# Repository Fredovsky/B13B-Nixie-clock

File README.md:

# B13B-Nixie-clock
Nixie clock made from F9057 Nixie tubes (B13B sockets).

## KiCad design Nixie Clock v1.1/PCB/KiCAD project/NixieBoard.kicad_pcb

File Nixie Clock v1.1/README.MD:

# Nixie Tube Desk Clock

A beautiful 4-digit nixie tube clock powered by an ATmega328P microcontroller, featuring automatic brightness adjustment and anti-cathode poisoning routines.

## Features

- **4-Digit Time Display**: Shows hours and minutes in HH:MM format
- **Automatic Brightness Control**: Gradually adjusts brightness throughout the day based on time (no light sensor required)
- **Cathode Poisoning Prevention**: Automatic cleaning cycles to maintain nixie tube health
  - Short cycle every hour (15 seconds)
  - Long cycle daily at 3:00 AM (30 minutes)
- **Simple Time Setting**: Two-button interface (Hour/Minute) with auto-repeat on long press
- **RTC Backup**: DS3231 real-time clock with battery backup maintains accurate time
- **Visual Error Indicators**: Blinking display indicates RTC issues or power loss

## Version 1.1 Changes

This version (v1.1) includes several improvements over v1.0:

### Hardware Changes
- **Simplified button interface**: 2 buttons (Hour/Minute) instead of 3 (Mode/+/-)
- **Removed brightness sensor**: Automatic brightness adjustment is now time-based via software
- **Display mode**: Time only (no date/year display modes)
- **PCB redesign**: Now in KiCad format (previously Eagle)

### Software Improvements
- Restored and improved blinking functionality for error indication
- Removed blocking delays from button handling for better responsiveness
- Implemented proper auto-repeat for time adjustment buttons
- Added RTC communication error detection
- Cleaned up code structure with named constants
- Optimized SPI communication
- Fixed potential brightness range bugs

*Code cleaned and improved with assistance from Claude AI*

## Hardware Components

### Main Festures
- **Microcontroller**: ATmega328P
- **RTC Module**: DS3231 with CR2032 battery backup
- **Nixie Tubes**: 4× B31B socket tubes (10-digit tubes)
- **High Voltage Drivers**: 2× HV5530 (32-bit shift registers)

### Pin Assignments
```
Pin 6:  Hour button input
Pin 7:  Minute button input
Pin 9:  PWM output for brightness control
Pin 10: SPI latch pin for HV5530
Pin 11: SPI MOSI (to HV5530)
Pin 13: SPI SCK (to HV5530)
```

## Project Files

### PCB Design
The `PCB/` folder contains:
- KiCad project files (.kicad_pro, .kicad_sch, .kicad_pcb)
- Gerber files for PCB manufacturing
- Bill of Materials (BOM)

### 3D Printed Case
The `3D Files/` folder contains:
- STL files for case components
- CAD source files

### Firmware
- `main.cpp`: Arduino-compatible C++ code for ATmega328P
- Uses Arduino framework with RTClib library (v1.12.4)

## Software Configuration

### Brightness Settings
Automatic brightness adjustment can be customized:

```cpp
uint8_t minBrightness = 15;        // Minimum PWM (0-255)
uint8_t maxBrightness = 240;       // Maximum PWM (0-255)
uint8_t timeStartDecrease = 19;    // Hour to start dimming (24h format)
uint8_t timeStartIncrease = 6;     // Hour to start brightening (24h format)
```

**How it works:**
- Brightness gradually decreases from 7 PM (19:00) to 6 AM
- Brightness gradually increases from 6 AM to 7 PM
- Changes by 1 PWM unit per minute (~3.75 hours for full transition)

### Cathode Poisoning Prevention
```cpp
constexpr uint8_t CLEANING_HOUR = 3;  // Hour for long cleaning cycle (3 AM)
```

The clock automatically cycles through all digits to prevent cathode poisoning:
- **Short cycle**: Every hour on the hour (except at cleaning hour) - 15 seconds
- **Long cycle**: Daily at 3:00 AM - 30 minutes

## Building and Uploading

### Requirements
- PlatformIO
- USBasp, Arduino as ISP, or similar programmer for ATmega328P

### Setting Initial Time
If the RTC has lost power (battery dead or first-time setup):
1. The display will show `00:00` blinking
2. Use Hour and Minute buttons to set the correct time
3. Blinking stops once you press a button (confirms time set)

## Usage

### Normal Operation
- Display shows current time in HH:MM format
- Brightness adjusts automatically throughout the day
- Cathode cleaning cycles run automatically

### Setting Time
- **Short press Hour button**: Increment hour by 1
- **Long press Hour button**: Auto-repeat (fast increment)
- **Short press Minute button**: Increment minute by 1
- **Long press Minute button**: Auto-repeat (fast increment)

### Error Indicators
- **Blinking 88:88**: RTC communication error
- **Blinking 00:00**: RTC lost power (battery dead or removed - set time)

## Troubleshooting

### Display shows 00:00 blinking
- Replace CR2032 battery in DS3231 module
- Set time using Hour/Minute buttons

### Tubes don't light up
- Check high voltage power supply (~170V)
- Verify HV5530 connections and power
- Test SPI communication (MOSI, SCK, Latch)

### Time drifts
- DS3231 is very accurate (±2ppm)
- Check RTC battery voltage
- Ensure crystal is functioning

## License

MIT License

Copyright (c) 2025 Frederic Lidove

Permission is hereby granted, free of charge, to any person obtaining a copy
of this software and associated documentation files (the "Software"), to deal
in the Software without restriction, including without limitation the rights
to use, copy, modify, merge, publish, distribute, sublicense, and/or sell
copies of the Software, and to permit persons to whom the Software is
furnished to do so, subject to the following conditions:

The above copyright notice and this permission notice shall be included in all
copies or substantial portions of the Software.

THE SOFTWARE IS PROVIDED "AS IS", WITHOUT WARRANTY OF ANY KIND, EXPRESS OR
IMPLIED, INCLUDING BUT NOT LIMITED TO THE WARRANTIES OF MERCHANTABILITY,
FITNESS FOR A PARTICULAR PURPOSE AND NONINFRINGEMENT.

## Credits

- Hardware design: Frederic Lidove
- Firmware v1.1: Code improvements by Claude AI (Anthropic)

## Changelog

### v1.1 (Current)
- Simplified to 2-button interface (H/M only)
- Removed hardware brightness sensor
- Implemented software-based automatic brightness adjustment
- Removed date/year display modes (time only)
- PCB redesigned in KiCad
- Code cleanup and optimization
- Improved error handling and blinking indicators

### v1.0
- Initial release
- 3-button interface (Mode/+/-)
- Hardware brightness sensor
- Date and year display modes
- Eagle PCB design

## Contributing

Contributions are welcome! Please feel free to submit pull requests or open issues for bugs and feature requests.

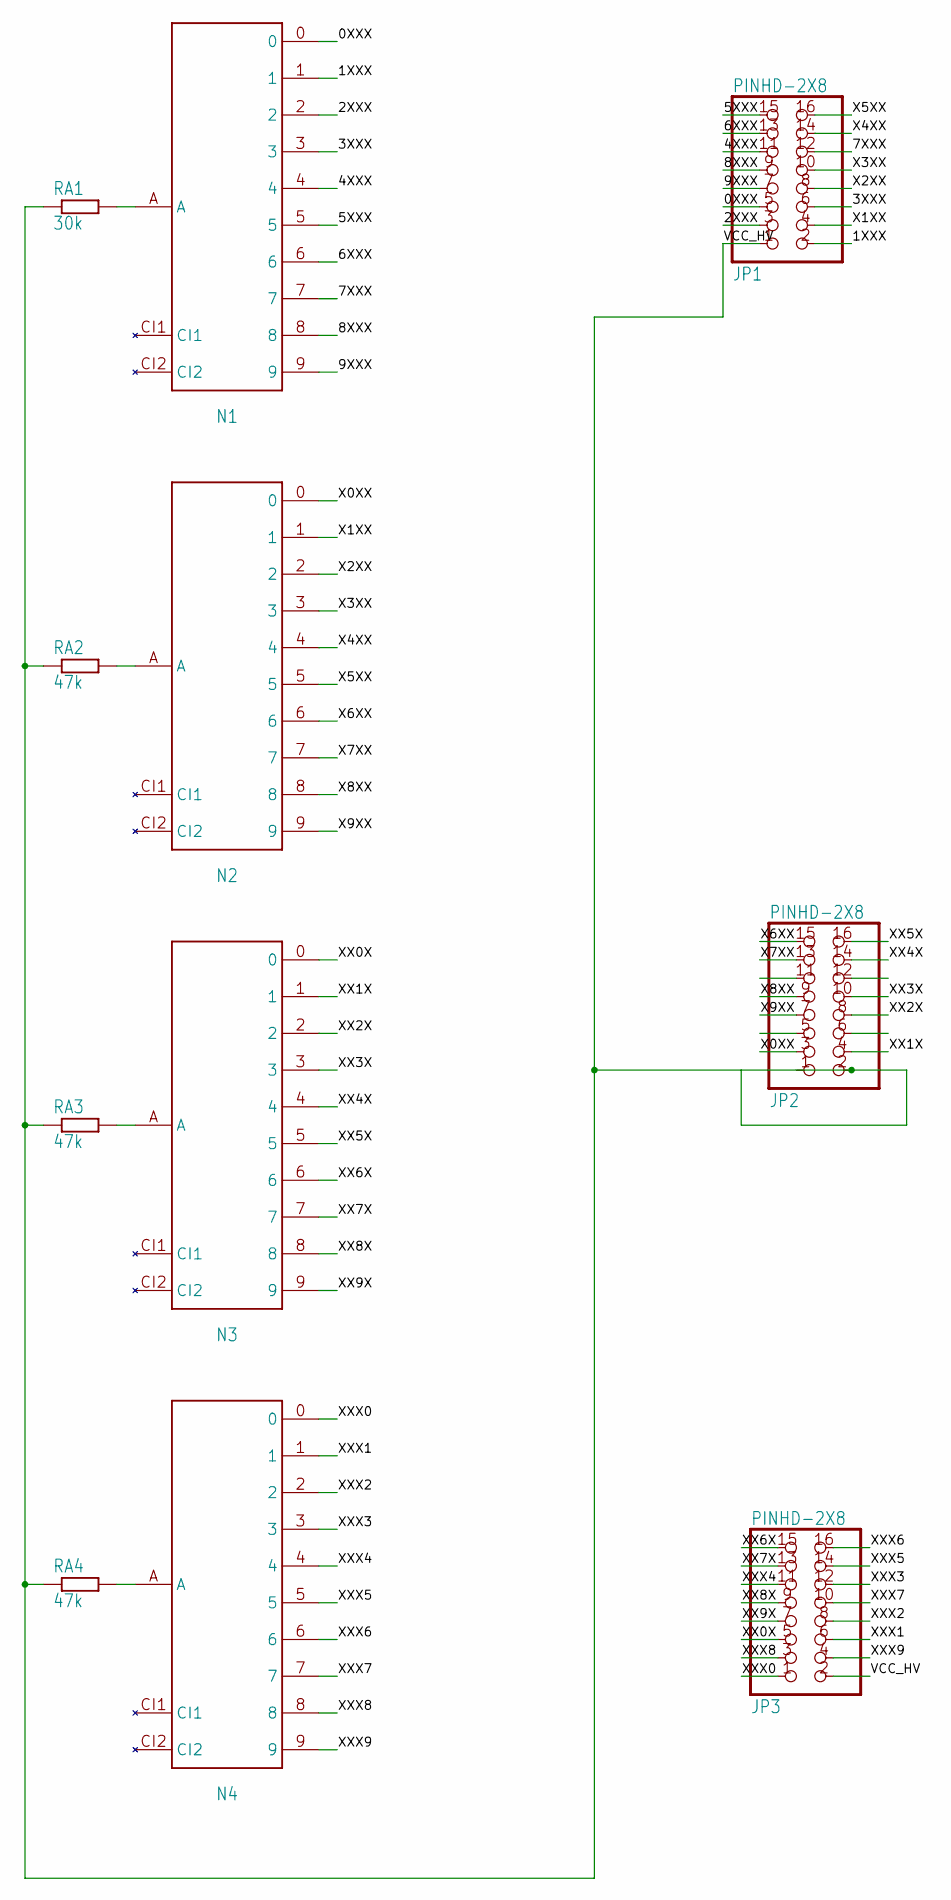
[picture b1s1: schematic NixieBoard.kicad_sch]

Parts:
JP1, JP2, JP3: PINHD-2X8; 2X08
N1, N2, N3, N4: F9057TUBE; F9057PIN
RA1: 30k; R2010
RA2, RA3, RA4: 47k; R2010

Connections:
0XXX: JP1.5, N1.0
1XXX: JP1.2, N1.1
2XXX: JP1.3, N1.2
3XXX: JP1.6, N1.3
4XXX: JP1.11, N1.4
5XXX: JP1.15, N1.5
6XXX: JP1.13, N1.6
7XXX: JP1.12, N1.7
8XXX: JP1.9, N1.8
9XXX: JP1.7, N1.9
unnamed: N4.A, RA4.2
unnamed: N3.A, RA3.2
unnamed: N2.A, RA2.2
unnamed: N1.A, RA1.2
VCC_HV: JP1.1, JP2.1, JP2.2, JP3.2, RA1.1, RA2.1, RA3.1, RA4.1
X0XX: JP2.3, N2.0
X1XX: JP1.4, N2.1
X2XX: JP1.8, N2.2
X3XX: JP1.10, N2.3
X4XX: JP1.14, N2.4
X5XX: JP1.16, N2.5
X6XX: JP2.15, N2.6
X7XX: JP2.13, N2.7
X8XX: JP2.9, N2.8
X9XX: JP2.7, N2.9
XX0X: JP3.5, N3.0
XX1X: JP2.4, N3.1
XX2X: JP2.8, N3.2
XX3X: JP2.10, N3.3
XX4X: JP2.14, N3.4
XX5X: JP2.16, N3.5
XX6X: JP3.15, N3.6
XX7X: JP3.13, N3.7
XX8X: JP3.9, N3.8
XX9X: JP3.7, N3.9
XXX0: JP3.1, N4.0
XXX1: JP3.6, N4.1
XXX2: JP3.8, N4.2
XXX3: JP3.12, N4.3
XXX4: JP3.11, N4.4
XXX5: JP3.14, N4.5
XXX6: JP3.16, N4.6
XXX7: JP3.10, N4.7
XXX8: JP3.3, N4.8
XXX9: JP3.4, N4.9

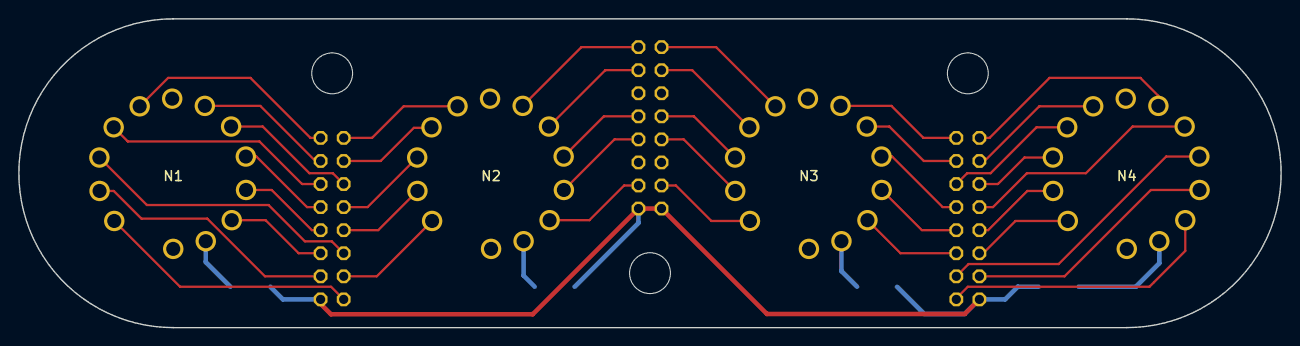
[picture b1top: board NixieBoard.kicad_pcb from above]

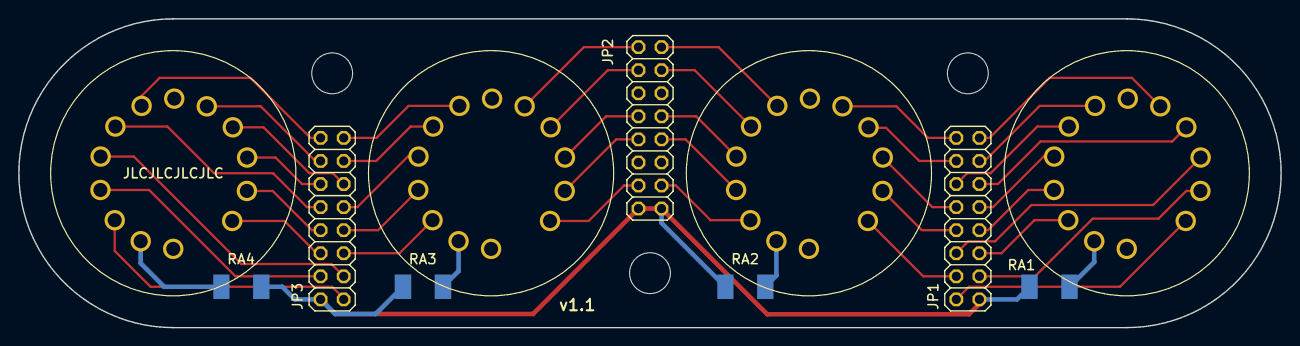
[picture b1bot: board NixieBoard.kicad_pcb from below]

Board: 2 copper layers, 139.0 x 34.0 mm, 14 parts (7 on the bottom side), 45 nets.

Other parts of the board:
UNK_HOLE_0: dummyfp0
UNK_HOLE_1: dummyfp1
UNK_HOLE_2: dummyfp2

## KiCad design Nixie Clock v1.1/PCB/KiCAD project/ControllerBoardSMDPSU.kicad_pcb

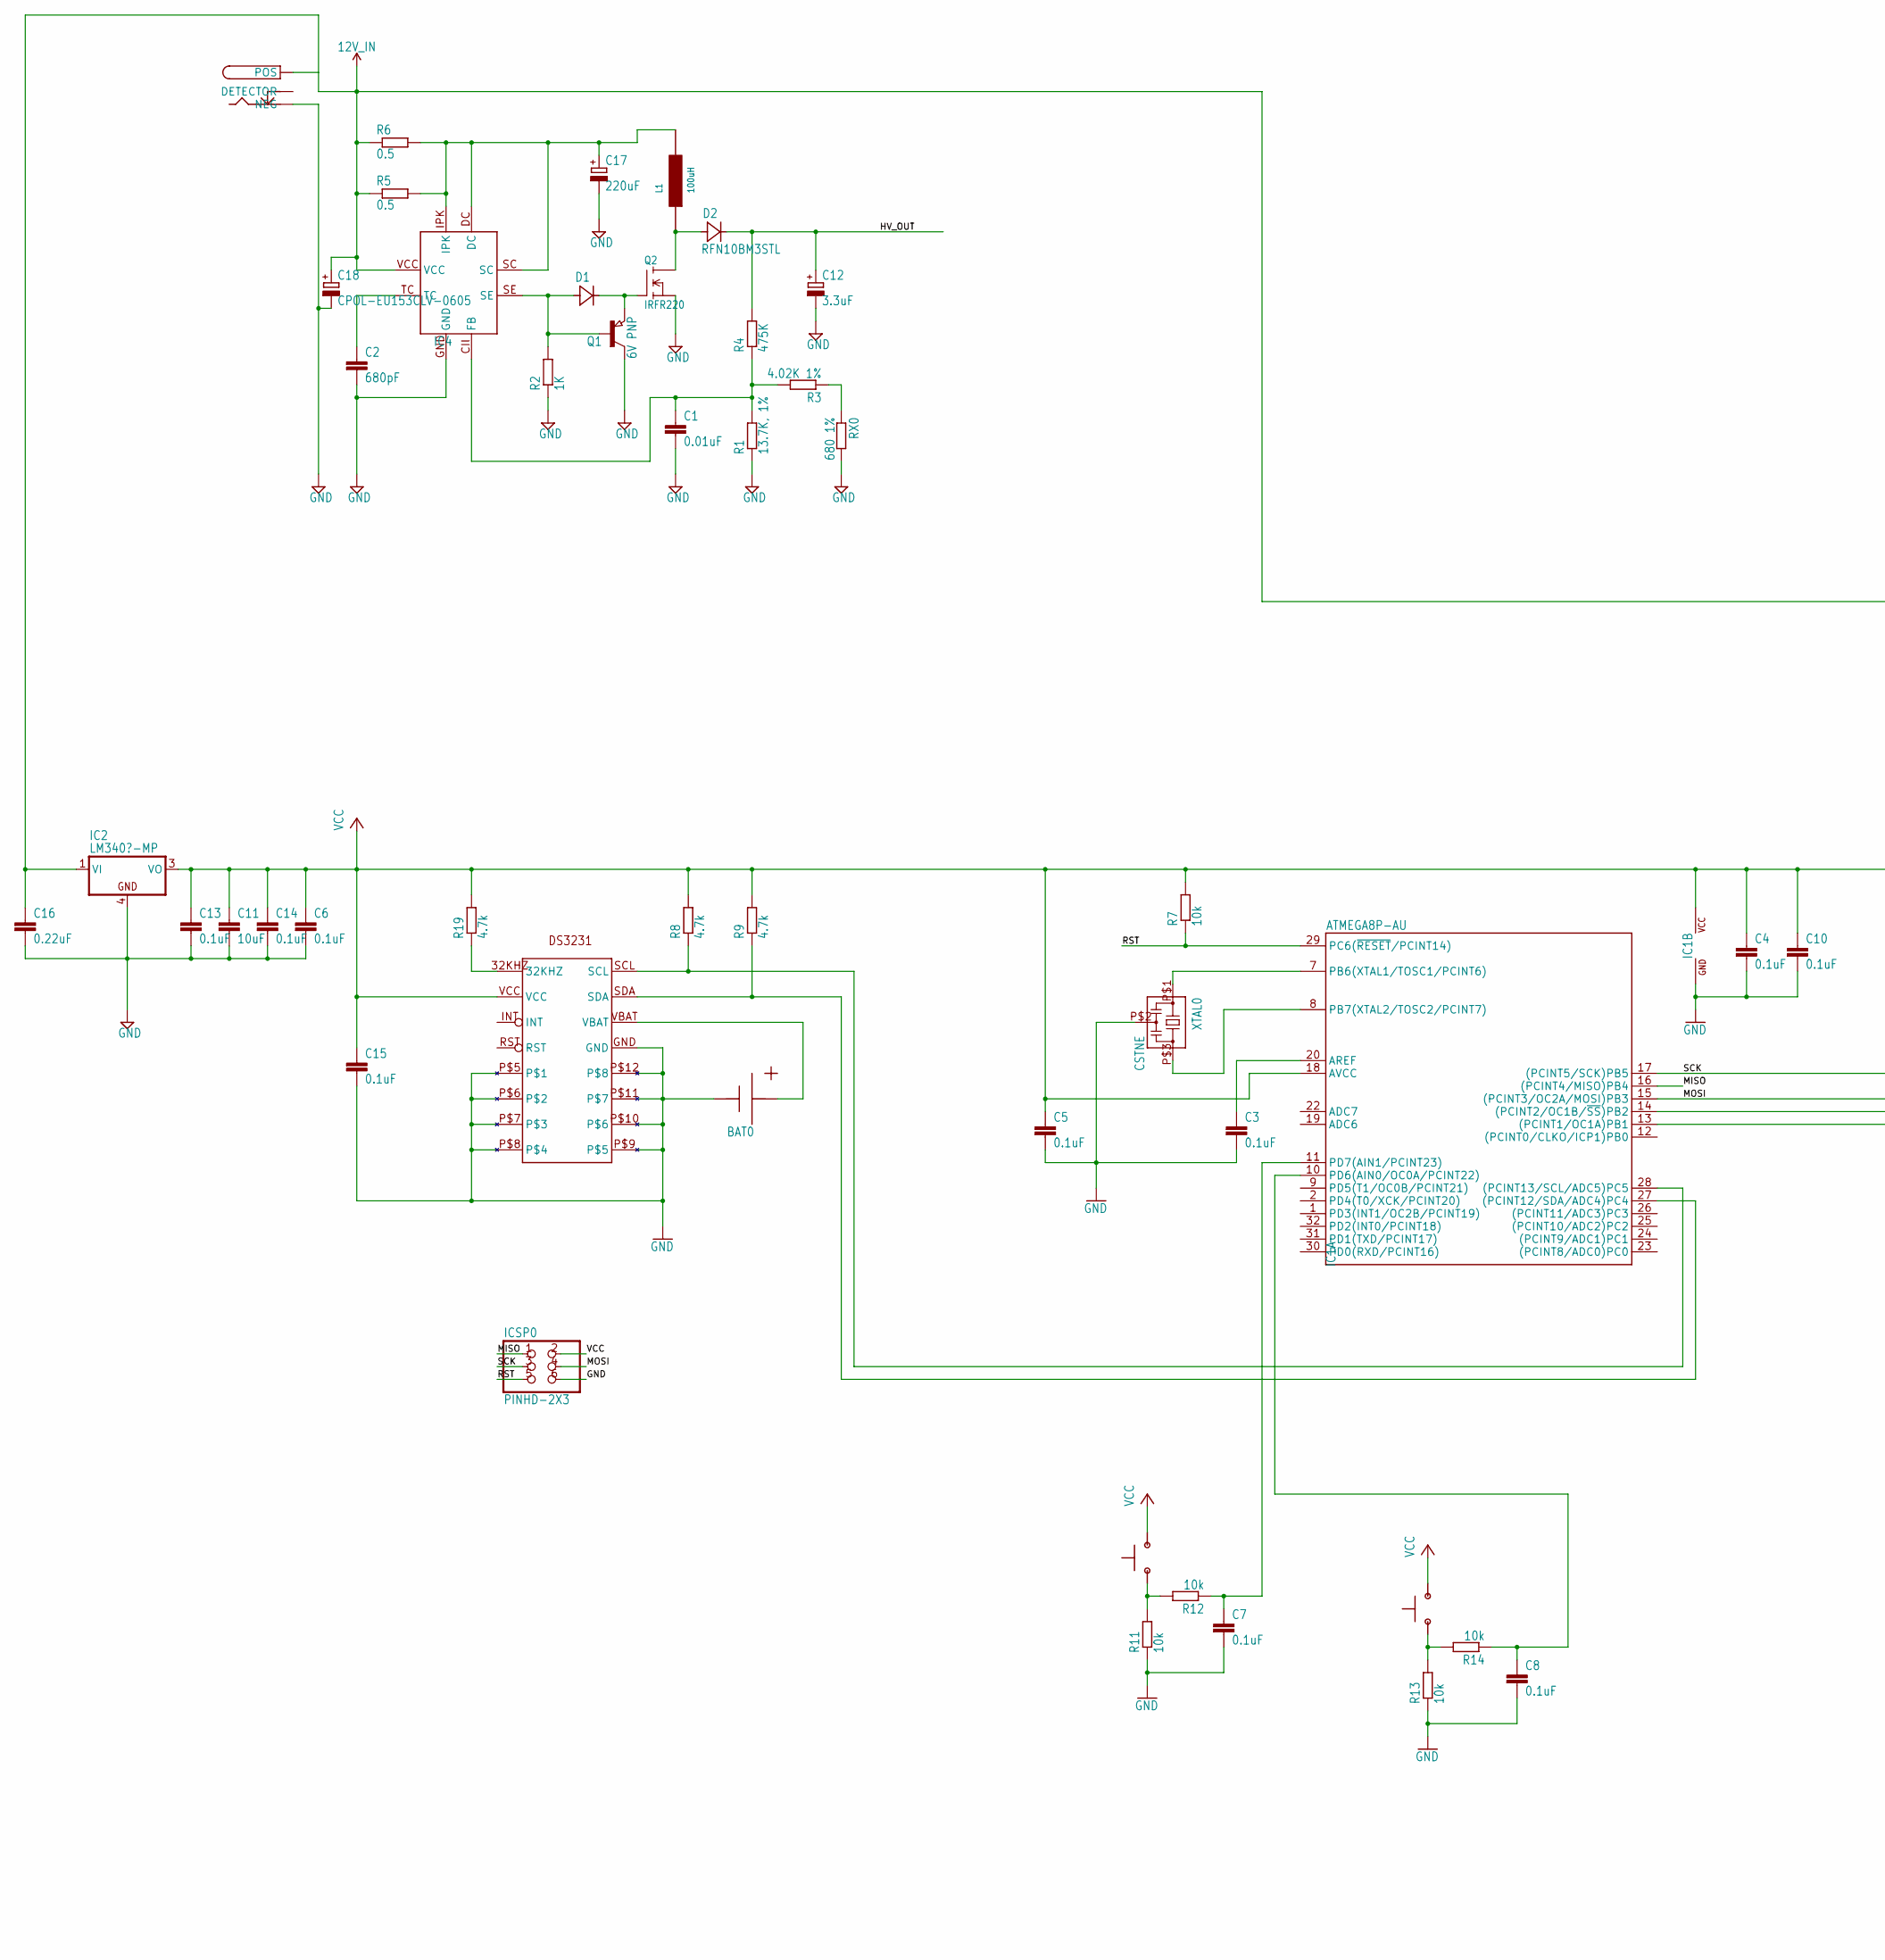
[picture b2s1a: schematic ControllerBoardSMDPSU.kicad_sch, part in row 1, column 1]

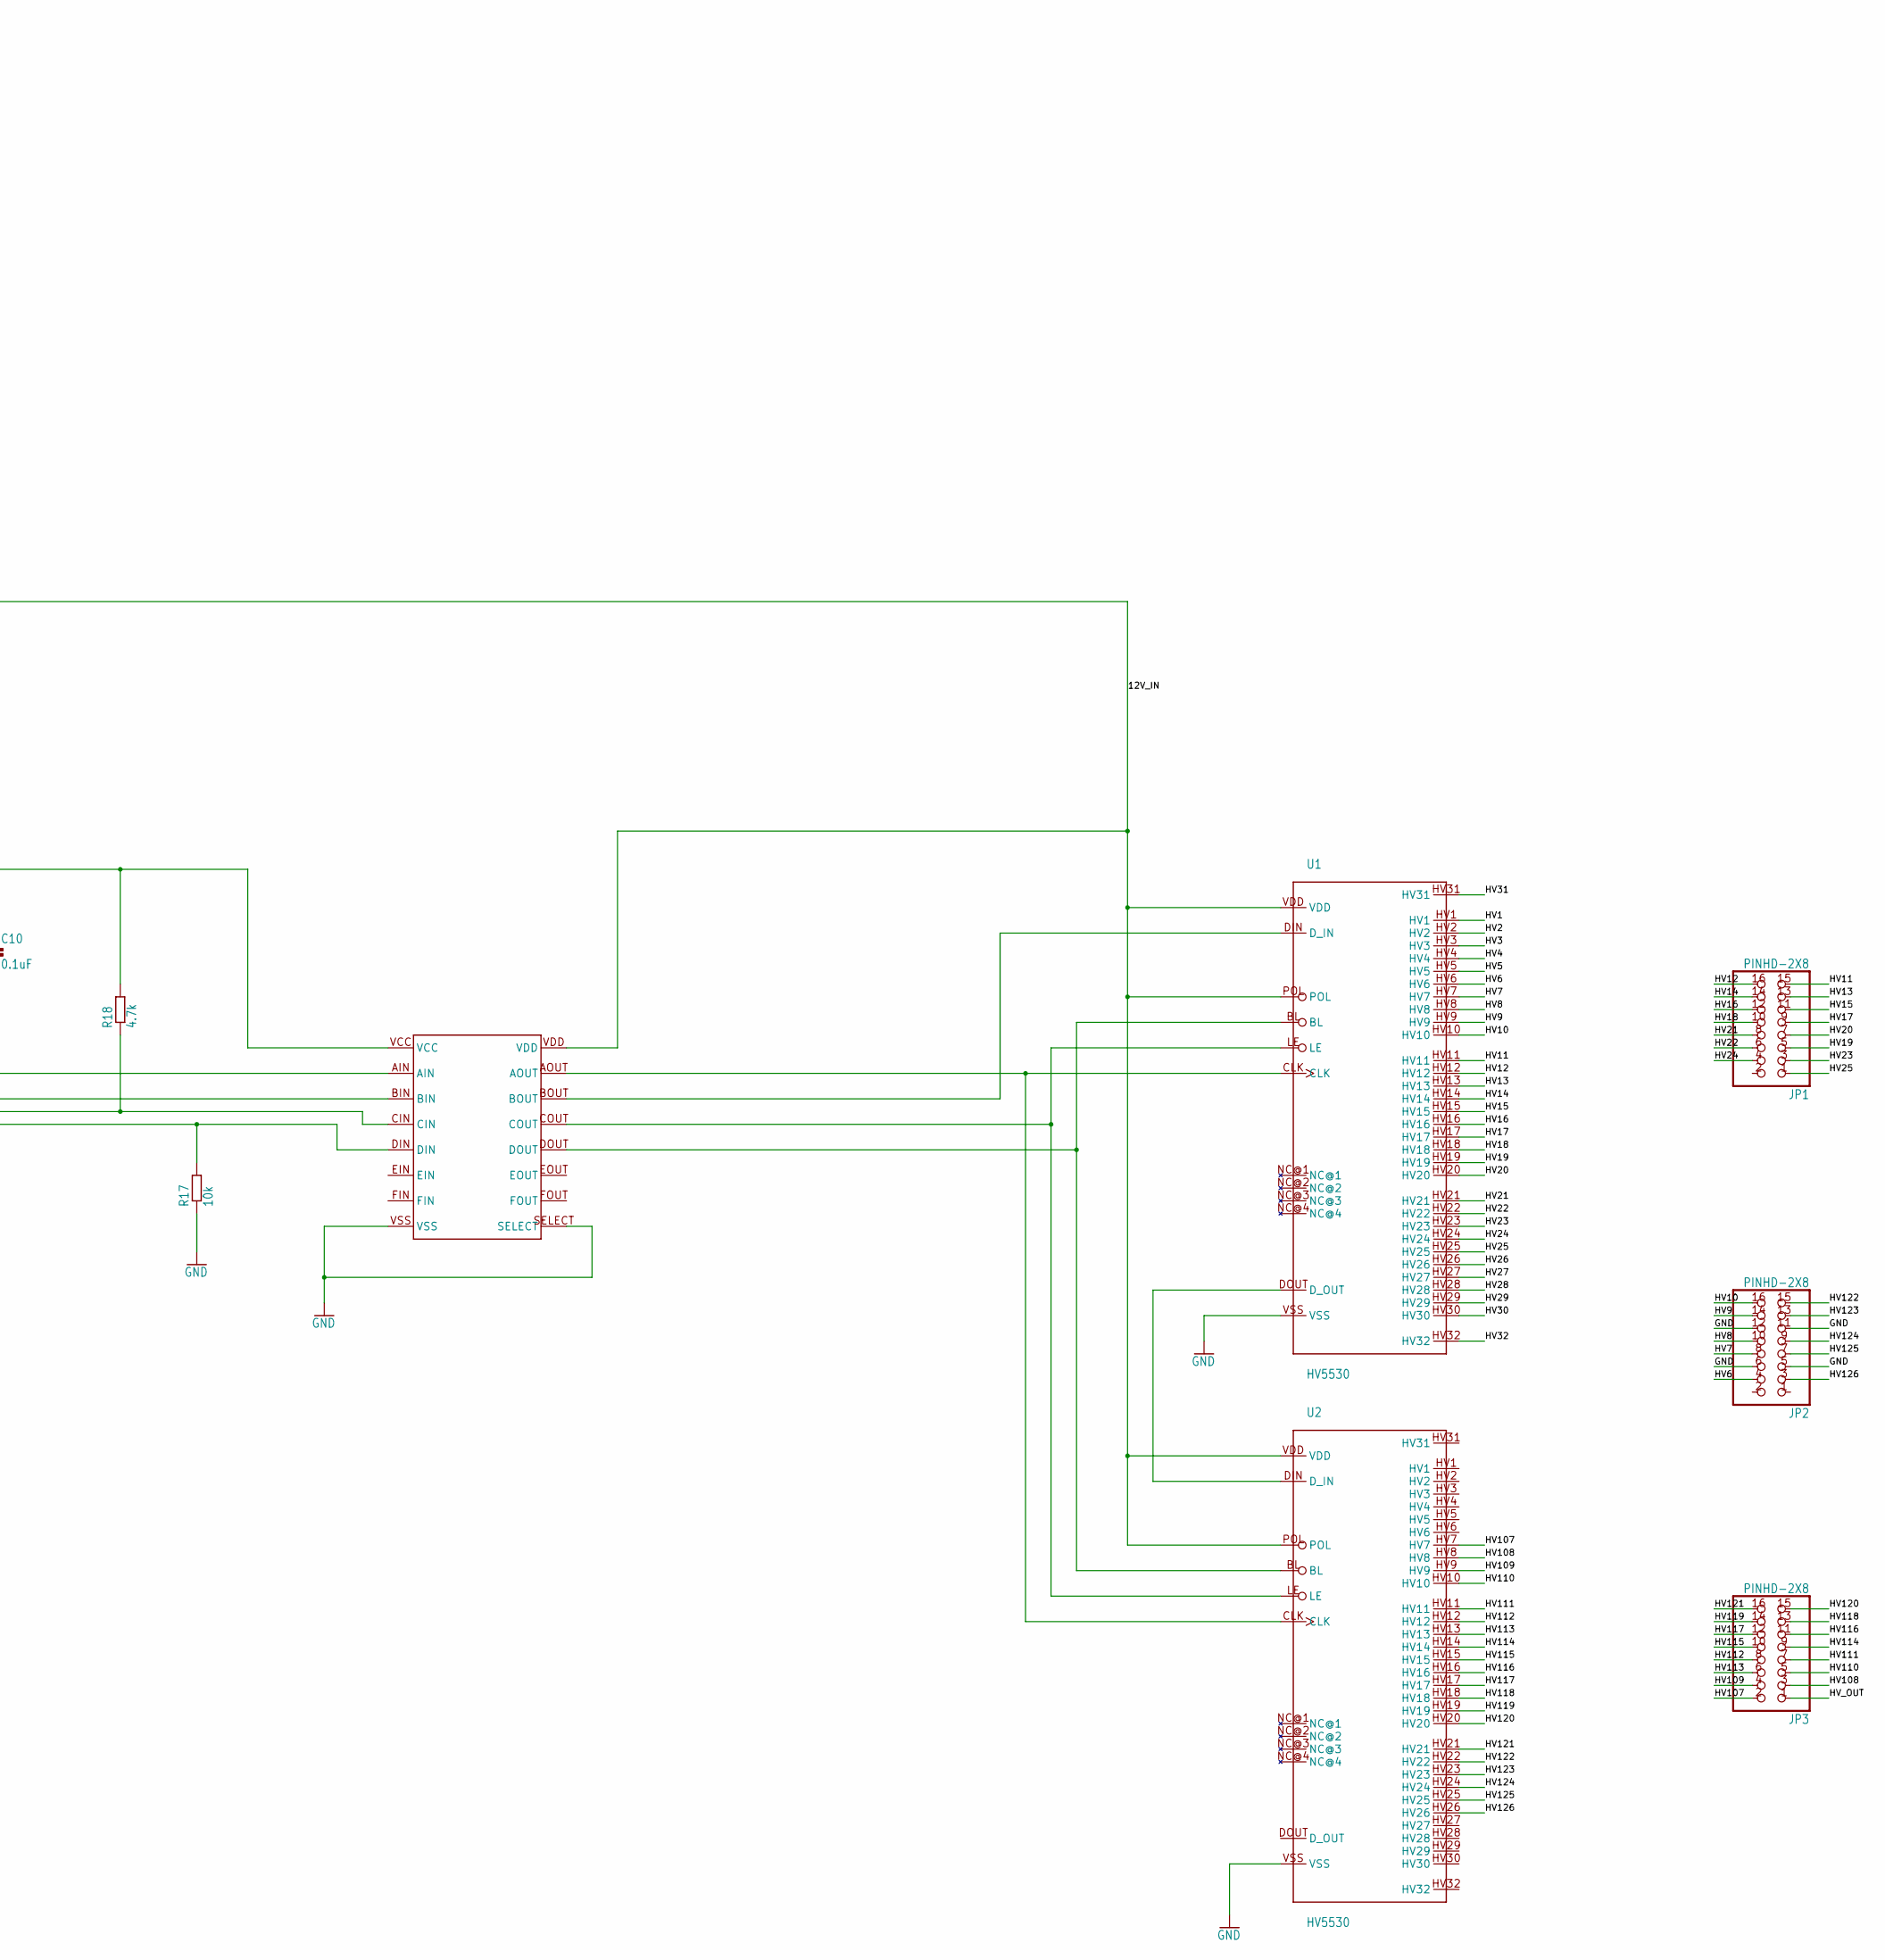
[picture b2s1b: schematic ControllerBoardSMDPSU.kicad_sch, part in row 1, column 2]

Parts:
BAT0: CR2032-SMD-HLDR; CR2032-SMD
C1: 0.01uF; C0603
C2: 680pF; C0603
C3, C4, C5, C6, C7, C8, C10, C13, C14, C15: 0.1uF; C0603
C11: 10uF; C0603
C12: 3.3uF; 153CLV-0810
C16: 0.22uF; C0603
C17: 220uF; 153CLV-0605
C18: CPOL-EU153CLV-0605; 153CLV-0605
D1: SOT123DIODE; SOD123
D2: RFN10BM3STL; TO252
IC1: ATMEGA8P-AU; QFP32_7X7_0.80
IC2: LM340?-MP; SOT223
IC3: CD4504BTSSOP16; SOP65P640X120-16N
IC4: MC34063; SOIC127P600X175-8
ICSP0: PINHD-2X3; 2X03
JP1, JP2, JP3: PINHD-2X8; 2X08
L1: 100uH; SDR1105
Q1: 6V PNP; SOT23
Q2: IRFR220; DPAK
R1: 13.7K, 1%; R1206
R2: 1K; R1206
R3: 4.02K 1%; R1206
R4: 475K; R1206
R5, R6: 0.5; R1206
R7, R11, R12, R13, R14, R17: 10k; R0603
R8, R9, R18, R19: 4.7k; R0603
RTC0: DS3231-CORRECT; SOIC16-CORRECT
RX0: 680 1%; R1206
S1, S2: TL1105
U1, U2: HV5530; 44_PQFP_CORRECTED
UNK12V0: CUI_PWR_JACK
XTAL0: CSTNE

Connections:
12V_IN: C16.1, C18.+, IC2.1 (VI), IC3.VDD, IC4.VCC, R5.1, R6.1, U1.POL, U1.VDD, U2.POL, U2.VDD, UNK12V0.POS, UNK12V0.POS1 (POS); also elsewhere on the board
/HV1: U1.HV1
/HV2: U1.HV2
/HV3: U1.HV3
/HV4: U1.HV4
/HV5: U1.HV5
/HV6: JP2.4, U1.HV6
/HV7: JP2.8, U1.HV7
/HV8: JP2.10, U1.HV8
/HV9: JP2.14, U1.HV9
/HV10: JP2.16, U1.HV10
/HV11: JP1.15, U1.HV11
/HV12: JP1.16, U1.HV12
/HV13: JP1.13, U1.HV13
/HV14: JP1.14, U1.HV14
/HV15: JP1.11, U1.HV15
/HV16: JP1.12, U1.HV16
/HV17: JP1.9, U1.HV17
/HV18: JP1.10, U1.HV18
/HV19: JP1.5, U1.HV19
/HV20: JP1.7, U1.HV20
/HV21: JP1.8, U1.HV21
/HV22: JP1.6, U1.HV22
/HV23: JP1.3, U1.HV23
/HV24: JP1.4, U1.HV24
/HV25: JP1.1, U1.HV25
/HV26: U1.HV26
/HV27: U1.HV27
/HV28: U1.HV28
/HV29: U1.HV29
/HV30: U1.HV30
/HV31: U1.HV31
/HV32: U1.HV32
/HV107: JP3.2, U2.HV7
/HV108: JP3.3, U2.HV8
/HV109: JP3.4, U2.HV9
/HV110: JP3.5, U2.HV10
/HV111: JP3.7, U2.HV11
/HV112: JP3.8, U2.HV12
/HV113: JP3.6, U2.HV13
/HV114: JP3.9, U2.HV14
/HV115: JP3.10, U2.HV15
/HV116: JP3.11, U2.HV16
/HV117: JP3.12, U2.HV17
/HV118: JP3.13, U2.HV18
/HV119: JP3.14, U2.HV19
/HV120: JP3.15, U2.HV20
/HV121: JP3.16, U2.HV21
/HV122: JP2.15, U2.HV22
/HV123: JP2.13, U2.HV23
/HV124: JP2.9, U2.HV24
/HV125: JP2.7, U2.HV25
/HV126: JP2.3, U2.HV26
/HV_OUT: C12.+, D2.3 (C), JP3.1, R4.2
/MISO: IC1.16 ((PCINT4/MISO)PB4), ICSP0.1; also elsewhere on the board
/MOSI: IC1.15 ((PCINT3/OC2A/MOSI)PB3), IC3.BIN, ICSP0.4; also elsewhere on the board
/RST: IC1.29 (PC6(~RESET/PCINT14)), ICSP0.5, R7.1; also elsewhere on the board
/SCK: IC1.17 ((PCINT5/SCK)PB5), IC3.AIN, ICSP0.3; also elsewhere on the board
GND: BAT0.NEG, C1.2, C2.2, C3.2, C4.2, C5.2, C6.2, C7.2, C8.2, C10.2, C11.2, C12.-, C13.2, C14.2, C15.2, C16.2, C17.-, C18.-, IC1.3 (GND), IC1.5 (GND), IC1.21 (GND), IC2.4 (GND), IC3.SELECT, IC3.VSS, IC4.GND, ICSP0.6, JP2.5, JP2.6, JP2.11, JP2.12, Q1.3 (C), Q2.3 (S), R1.1, R2.1, R11.1, R13.1, R17.1, RTC0.GND, RTC0.P$5, RTC0.P$6, RTC0.P$7, RTC0.P$8, RTC0.P$9, RTC0.P$10, RTC0.P$11, RTC0.P$12, RX0.2, U1.VSS, U2.VSS, UNK12V0.NEG, UNK12V0.NEG1 (NEG), XTAL0.P$2 (2); also elsewhere on the board
unnamed 59: BAT0.POS@1 (POS), BAT0.POS@2 (POS), RTC0.VBAT; also elsewhere on the board
unnamed: C2.1, IC4.TC
unnamed: C17.+, IC4.DC, IC4.IPK, IC4.SC, L1.P$2, R5.2, R6.2
unnamed: D1.2 (A), IC4.SE, Q1.1 (B), R2.2
unnamed: D1.1 (C), Q1.2 (E), Q2.1 (G)
unnamed: IC1.13 ((PCINT1/OC1A)PB1), IC3.DIN, R17.2
unnamed: IC1.14 ((PCINT2/OC1B/~SS)PB2), IC3.CIN, R18.1
unnamed 66: IC1.27 ((PCINT12/SDA/ADC4)PC4), R9.1, RTC0.SDA; also elsewhere on the board
unnamed 67: IC1.28 ((PCINT13/SCL/ADC5)PC5), R8.1, RTC0.SCL; also elsewhere on the board
unnamed: C3.1, IC1.20 (AREF)
unnamed 69: IC1.7 (PB6(XTAL1/TOSC1/PCINT6)), XTAL0.P$1 (1); also elsewhere on the board
unnamed 70: IC1.8 (PB7(XTAL2/TOSC2/PCINT7)), XTAL0.P$3 (3); also elsewhere on the board
unnamed: C8.1, IC1.10 (PD6(AIN0/OC0A/PCINT22)), R14.1
unnamed: C7.1, IC1.11 (PD7(AIN1/PCINT23)), R12.1
unnamed: IC3.AOUT, U1.CLK, U2.CLK
unnamed: IC3.COUT, U1.LE, U2.LE
unnamed: IC3.DOUT, U1.BL, U2.BL
unnamed: C1.1, IC4.CII (FB), R1.2, R3.2, R4.1
unnamed: D2.1 (A), D2.2 (A), L1.P$1, Q2.2 (D)
unnamed 78: R3.1, RX0.1; also elsewhere on the board
unnamed: R11.2, R12.2, S1.1, S1.2
unnamed: R13.2, R14.2, S2.1, S2.2
unnamed 81: R19.1, RTC0.32KHZ; also elsewhere on the board
unnamed: IC3.BOUT, U1.DIN (D_IN)
unnamed: U1.DOUT (D_OUT), U2.DIN (D_IN)
unnamed: UNK12V0.DETECTOR, UNK12V0.DETECTOR1 (DETECTOR)
VCC: C4.1, C5.1, C6.1, C10.1, C11.1, C13.1, C14.1, C15.1, IC1.4 (VCC), IC1.6 (VCC), IC1.18 (AVCC), IC2.3 (VO), IC3.VCC, R7.2, R8.2, R9.2, R18.2, R19.2, RTC0.VCC, S1.3, S1.4, S2.3, S2.4; also elsewhere on the board

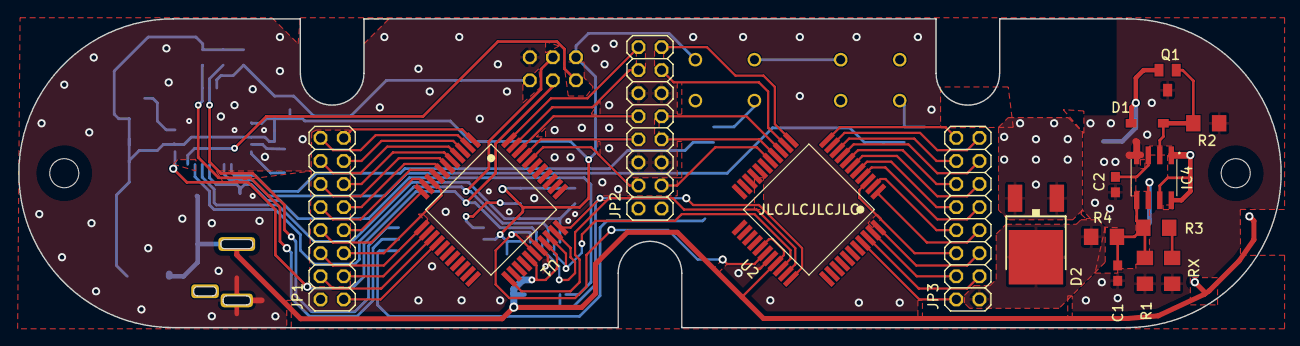
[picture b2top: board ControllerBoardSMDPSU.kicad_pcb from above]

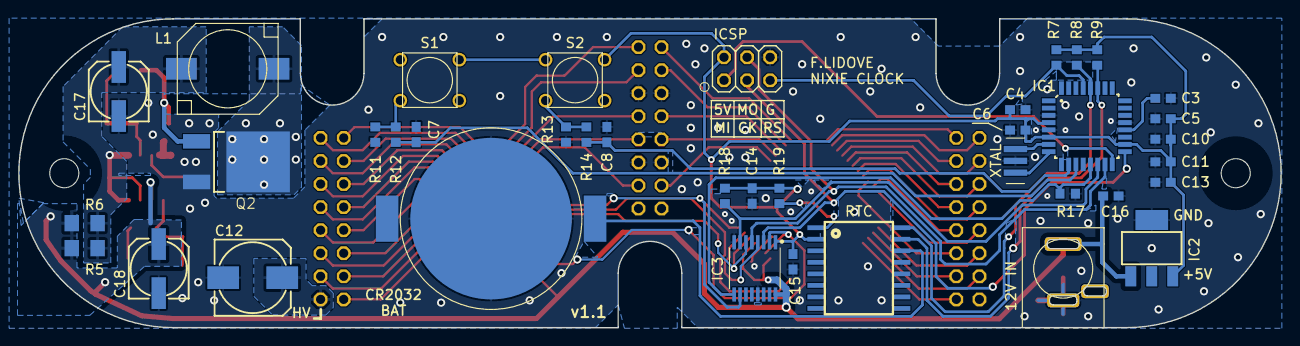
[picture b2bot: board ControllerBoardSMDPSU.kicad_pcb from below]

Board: 2 copper layers, 139.0 x 34.0 mm, 55 parts (39 on the bottom side), 74 nets.

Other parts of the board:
12V IN: CUI_PWR_JACK
ICSP: PINHD-2X3; 2X03_325
RTC: DS3231-CORRECT; SOIC16-CORRECT
RX: 680 1%; R1206_334
XTAL: CSTNE

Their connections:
12V_IN: 12V IN.POS, 12V IN.POS1 (POS); also elsewhere on the board
/MISO: ICSP.1; also elsewhere on the board
/MOSI: ICSP.4; also elsewhere on the board
/RST: ICSP.5; also elsewhere on the board
/SCK: ICSP.3; also elsewhere on the board
GND: 12V IN.NEG, 12V IN.NEG1 (NEG), ICSP.6, RTC.GND, RX.2, XTAL.P$2 (2); also elsewhere on the board
unnamed 59: RTC.VBAT; also elsewhere on the board
unnamed 66: RTC.SDA; also elsewhere on the board
unnamed 67: RTC.SCL; also elsewhere on the board
unnamed 69: XTAL.P$1 (1); also elsewhere on the board
unnamed 70: XTAL.P$3 (3); also elsewhere on the board
unnamed 78: RX.1; also elsewhere on the board
unnamed 81: RTC.32KHZ; also elsewhere on the board
unnamed: 12V IN.DETECTOR, 12V IN.DETECTOR1 (DETECTOR)
VCC: ICSP.2, RTC.VCC; also elsewhere on the board

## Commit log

2021-03-23 Project creation
    Added all project files.
2021-03-23 Reorganized files and added PCB BOM.
    Bill of materials added for V1 of the clock PCB using SMD for PSU.
2021-12-12 First flash CPU clock bug fix
    RTCLib version added and CPU clock speed protocol for first upload.
2021-12-23 Update main.cpp
    Long Cathode Poisoning Prevention Routine set for 30min at 3am, short routine every hour for 15 seconds.
2025-10-16 Added v1.1
    v1.1 = modified Control board and back board for simpler 2-buttons set up (no more date/year functionnality as it was useless).
    PCBs now all on KiCAD.
    Added an updated BOM and 3D Print files if unable to make wooden case.
2025-12-12 Set CPU frequency to 16MHz and configure fuses
    Updated CPU frequency to 16MHz and added fuse settings for external crystal.
2025-12-12 Add temporary file to Software directory
2025-12-12 Update README for Nixie Clock v1.1 changes
    V1.1 update removes a push button and light sensor, changes back button functions, and adjusts brightness automatically.
2025-12-12 Update README for Nixie Clock v1.1 features and changes
    Version 1.1 introduces a simplified interface and improved features, including automatic brightness adjustment and error handling.
2025-12-12 Refactor main.cpp for improved readability v1.1
    v1.1 Refactor main.cpp for improved readability and maintainability. Updated button handling, display logic, and constants for better clarity.
